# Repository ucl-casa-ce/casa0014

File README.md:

# CASA0014: CONNECTED ENVIRONMENTS

This is a test

## Summary

An introduction to building the internet of things for people and the environment. In this module students will be introduced to concepts and technologies underpinning connected environments and the role technology can play in trying to measure and understand the built and natural world. Through a series of practical workshop sessions students will be introduced to IoT prototyping tools, existing sensor systems in UCL East and the Queen Elizabeth Olympic Park and will build a simple sensor system to explore end to end IoT systems.

## Keywords
Internet of Things, Connected Environments, Prototypying, Living Labs

## What is in the CASA0014 GitHub repository?

This repo is being used to share materials used in the workshop component of the module. Some overview information is below but the key items are:

- links to [Vespera project folder](vespera)

- workshop - [Web LED](/webled/)

...

But for posterity we have also kept the old workshops for extra curricula activity!

- pre 2024 workshop - [blinking monster](/2023blinkingMonster/)

- pre 2024 workshop - [plant monitor](/2023plantMonitor/)

- 2024 workshop - [Chrono Lumina](/2024chronoLumina/)

## Module Aims and Objectives

After having taking this module, you will develop skills in three key areas and should be able to:

Domain Knowledge
- Understand the building blocks of of creating a connected environment (Internet of Things, IoT)
- Understand the various actors participating in our digitally connected environment
- Understand the context of IoT through work that has gone before and Living Lab environments

Prototyping Skills
- Create a simple Arduino sketch with a sensor input and / or actuator output
- Connect an Arduino based IoT device to a datastore to collect data over a wireless network
- Sketch, photograph and use rapid prototyping to explore ideas

Collaboration
- Provide peer feedback to fellow students on project work (a “learn, build, critique” approach will be used throughout the course)
- Create and present design decisions and prototypes to receive critical feedback
- Document and share project information to support reproducible research

In addition, you will establish a shared ‘connected environment’ that you will curate throughout the programme.

## Software

The course will make heavy use of the following software packages

- **Arduino** Download and install the [Arduino IDE](https://www.arduino.cc/en/main/software) Click the `JUST DOWNLOAD` link to the left of the `CONTRIBUTE & DOWNLOAD` button. Once downloaded follow the instructions to install.
    
- **GitHub** Create an account on [GitHub](https://github.com) if you don't already have one.

- **Git client.** If you are comfortable using Git on the command line then go for it. If you prefer a GUI representation then download a git client to make your life easier. 
    - We use [Tower](https://www.git-tower.com/) which has a [free version for students](https://www.git-tower.com/students/mac). 
    - We also hear good things about [SourceTree](https://www.sourcetreeapp.com) 
    - and there are a few other open source [GUI Clients here](https://git-scm.com/download/gui/windows)

## Main Module Information

All the week by week information is over on [Moodle](https://moodle.ucl.ac.uk/course/view.php?id=45126)

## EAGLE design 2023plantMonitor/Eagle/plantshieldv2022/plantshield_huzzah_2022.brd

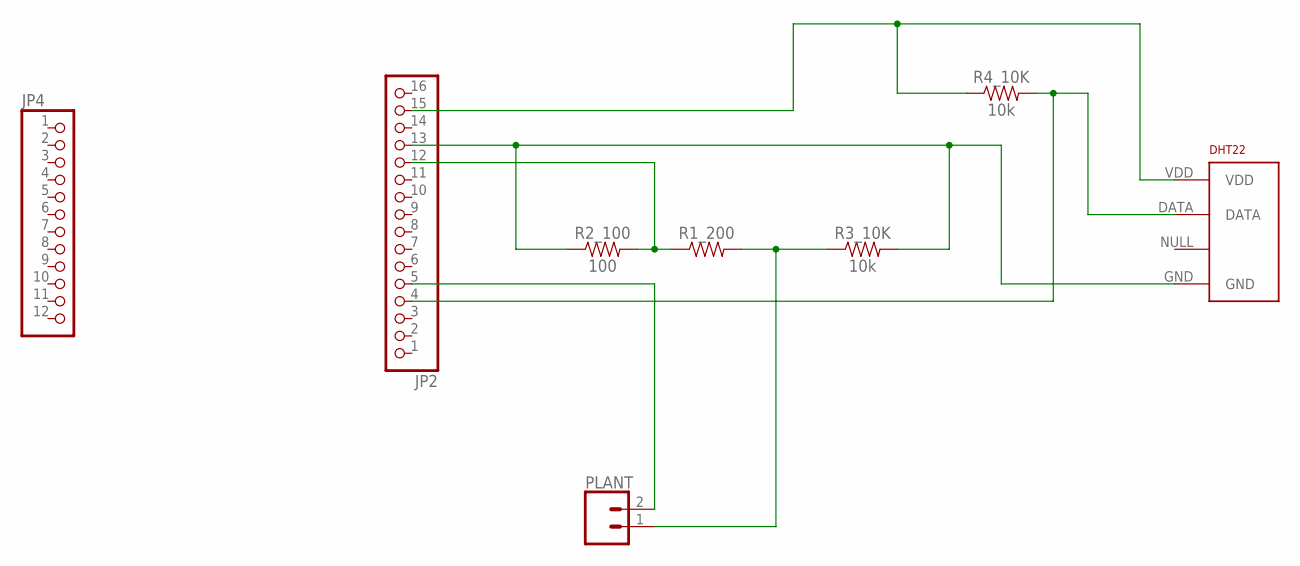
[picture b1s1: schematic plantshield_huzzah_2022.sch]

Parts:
DHT22: RHT03_DHT-22_AM2302; RHT03_DHT-22
JP2: HEADER-1X16ROUND; 1X16_ROUND
JP4: HEADER-1X12; 1X12_ROUND
PLANT: CONN_02; 1X02
R1_200: AXIAL-0.3
R2_100: 100; AXIAL-0.3
R3_10K, R4_10K: 10k; AXIAL-0.3

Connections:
unnamed: JP2.5, PLANT.2
unnamed: DHT22.DATA, JP2.4, R4_10K.P$2 (2)
unnamed: JP2.12, R1_200.P$1 (1), R2_100.P$2 (2)
unnamed: DHT22.VDD, JP2.15, R4_10K.P$1 (1)
unnamed: PLANT.1, R1_200.P$2 (2), R3_10K.P$1 (1)
unnamed: DHT22.GND, JP2.13, R2_100.P$1 (1), R3_10K.P$2 (2)

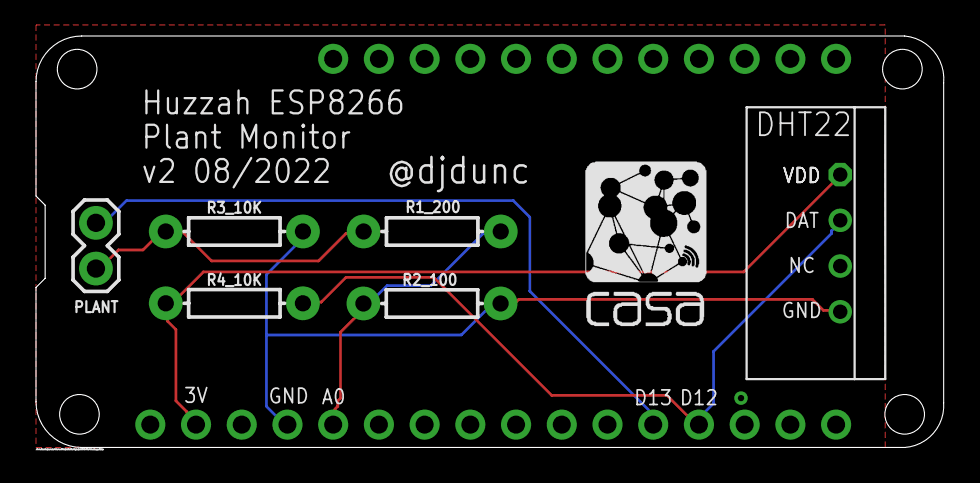
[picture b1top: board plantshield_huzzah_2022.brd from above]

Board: 2 copper layers, 50.4 x 22.9 mm, 8 parts (0 on the bottom side), 6 nets.

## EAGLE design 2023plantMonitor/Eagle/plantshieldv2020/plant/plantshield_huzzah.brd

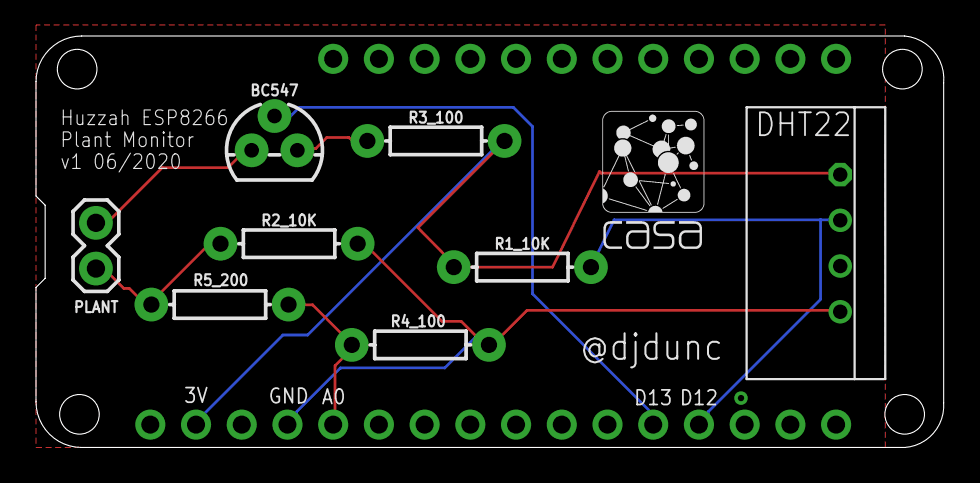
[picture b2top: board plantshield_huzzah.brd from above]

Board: 2 copper layers, 50.4 x 22.9 mm, 10 parts (0 on the bottom side), 8 nets.

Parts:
BC547: 200mA/40V; TO-92
DHT22: RHT03_DHT-22
JP2: 1X16_ROUND
JP4: 1X12_ROUND
PLANT: 1X02
R1_10K, R2_10K: 10k; AXIAL-0.3
R3_100, R4_100: 100; AXIAL-0.3
R5_200: AXIAL-0.3

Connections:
unnamed: BC547.2, JP2.5
unnamed: DHT22.DATA, JP2.4, R1_10K.P$2
unnamed: BC547.3, R3_100.P$1
unnamed: BC547.1, PLANT.2
unnamed: JP2.12, R4_100.P$2, R5_200.P$1
unnamed: DHT22.GND, JP2.13, R2_10K.P$2, R4_100.P$1
unnamed: PLANT.1, R2_10K.P$1, R5_200.P$2
unnamed: DHT22.VDD, JP2.15, R1_10K.P$1, R3_100.P$2

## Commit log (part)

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2021-07-02 blinking monster setup
2021-07-02 Plant monitor setup
2021-07-02 adding ignores
2021-08-18 telegraf conf file setup
    minimal example for plant monitor
2021-08-18 updating mqtt server
2021-08-18 making even simpler
2021-08-18 changing mqtt topics
2021-08-24 updating mqtt topic
2021-10-05 CountBat example added
2021-10-26 updated MQTT examples with new MQTT details
2021-10-27 smal change
2021-11-02 Updates to telegraf config
    updated the mqtt configuration settings to be used with the celab mqtt server and the naming conventions for the lab based plant monitors.
2021-11-02 minor update
2021-12-06 remove webserver
2021-12-06 deleting unwanted file
2021-12-06 example gitignore
2021-12-06 adding test ignore
2022-08-22 v2 updates
2022-08-23 minor typo
2022-09-23 adding page display for html
2022-09-27 ignore update
2022-10-13 update for InfluxDB v2
2022-10-14 InfluxDBv2 Dashboard sample
    example dashboard for casa0014 plant monitors
2022-10-14 workshop updates
2022-10-14 token change
2022-10-25 Main assets and description added
2023-10-18 2023 update
2024-09-23 2024 updates
2024-09-23 adding chrono lumina
2024-09-23 Python examples by Calli
2024-09-23 link updated
2024-09-23 v1.2 - uploaded to 50 ESP32-C3-Zero devices for CASA0014
2024-09-23 improving project overview
2024-09-23 minor
2024-09-23 applying stash
2024-09-23 readme updates
2024-10-04 web led added to repo
2024-10-04 adding link to web led
2024-10-09 Walkshop
2024-10-09 Add files via upload
    Add UHI sensor
2024-10-24 added final image
2024-10-25 neo pixel strip demo
2024-10-25 MKR1010 scketches
2024-10-25 removing retain messages
2024-10-26 added a couple more dev photos
2024-11-07 adding api.md
2025-09-01 Luminaire
    first push of the test code for the lumaire - getting basics setup
2025-09-01 notes on what is what
2025-09-08 Revise summary in README for IoT module
2025-09-08 reorg for start of 2025
2025-09-08 updating typo in link
2025-09-26 Vespera setup
2025-09-26 typos
2025-09-26 adding link to vespera for start of year
2025-10-03 reinstating webled folder
2025-10-04 adding workshop sketch for Vespera
2025-10-04 user selector code
2025-10-15 L6 updates
2025-10-15 L6 update
2025-10-15 adding url for plug
2025-10-18 Update readme with video link for Vespera
    Added a video link for the Vespera component.
2025-10-18 Fix HTML syntax in readme.md for video tag
2025-10-18 Fix video link formatting in readme.md
    Corrected video link formatting in the readme.
2025-10-18 Fix URL formatting in readme.md
2025-10-18 Embed YouTube video in Vespera readme
    Added an embedded YouTube video player for Vespera.
2025-10-18 Update YouTube links and descriptions in readme
2025-10-18 Enhance documentation for Vespera and Arduino Dial
    Updated the readme to clarify the functionality of the Arduino Dial and the web visualizer, and added details on how to test code with and without Vespera.
2025-10-18 Add Flickr link to readme.md
2025-10-21 controller was freezing
    The controller was stopping when it lost wifi connection so an additional check added on the main loop to catch a dropped connection. Also noticed that the code for the mqtt connection was “blocking”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
2025-10-22 Reducing subscriptions to one vs all
    Realised that subscribing to all the topics but only showing the “current” had the potential to overload the arduino with volume of topics it was having to process. Changed the code so that it now on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
2025-10-22 test commit
2025-10-22 Clean up README by removing test text
    Removed introductory test text from README.

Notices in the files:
parts and their libraries:
SparkFun-DiscreteSemi: Licensing: Creative Commons ShareAlike 4.0 International - https://creativecommons.org/licenses/by-sa/4.0
microbuilder: This work is placed in the public domain, and may be freely used for commercial and non-commercial work with the following conditions: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
